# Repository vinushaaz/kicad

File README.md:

# KiCad PCB Design Journey

## About
This repository contains my learning and projects in PCB design using KiCad.  
It shows my progress from basic schematics to complete PCB layouts.

## Tools
- KiCad
- GitHub
- Arduino / Microcontrollers

## Skills Gained
- Schematic design
- Footprint assignment
- PCB layout & routing
- Design Rule Check (DRC)
- Gerber file generation

## Projects
- Queaky Toy circuit
- LED Blinker PCB  
- 4x4 Keypad Interface  
- LCD Interface Circuit  

## Goal
To design and build reliable PCBs for embedded and IoT applications.

## Author
Vinu – Embedded Systems | C/C++ | IoT

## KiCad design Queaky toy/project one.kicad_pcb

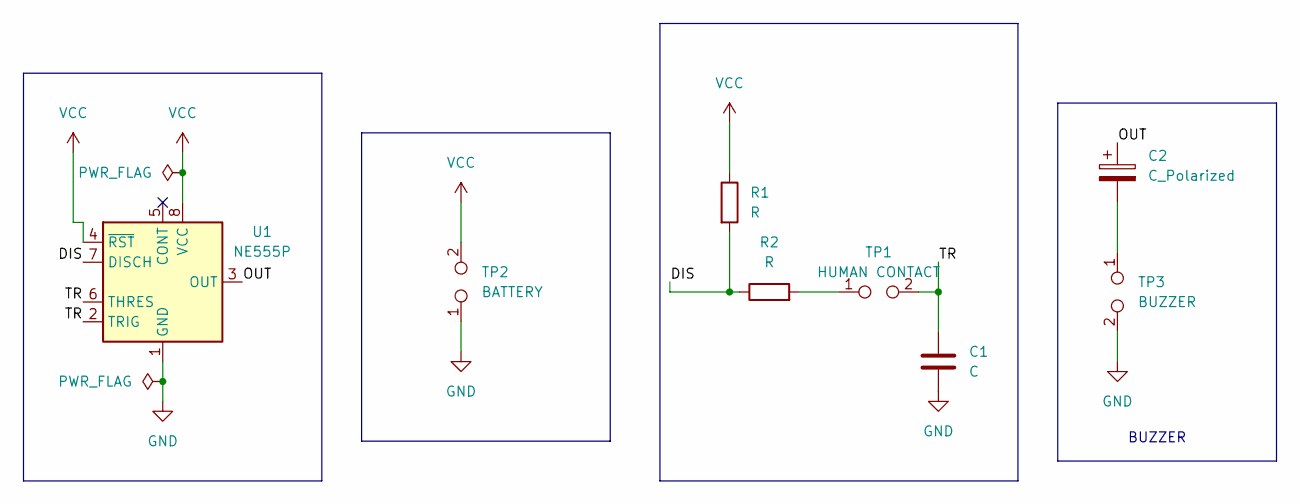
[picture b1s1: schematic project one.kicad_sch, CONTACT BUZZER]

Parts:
C1: C; C_Disc_D7.0mm_W2.5mm_P5.00mm
C2: C_Polarized; CP_Radial_D12.5mm_P5.00mm
R1, R2: R; R_Axial_DIN0309_L9.0mm_D3.2mm_P2.54mm_Vertical
TP1: HUMAN CONTACT; PinSocket_1x02_P2.54mm_Horizontal
TP2: BATTERY; PinSocket_1x02_P2.54mm_Horizontal
TP3: BUZZER; PinSocket_1x02_P2.54mm_Horizontal
U1: NE555P; DIP-8_W7.62mm

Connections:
/DIS: R1.2, R2.1, U1.7 (DISCH)
/OUT: C2.1, U1.3 (OUT)
GND: C1.2, TP2.1, TP3.2, U1.1 (GND)
unnamed: C2.2, TP3.1
unnamed: R2.2, TP1.1
VCC: C1.1, R1.1, TP1.2, TP2.2, U1.2 (TRIG), U1.4 (~RST), U1.6 (THRES), U1.8 (VCC)

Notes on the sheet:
BUZZER

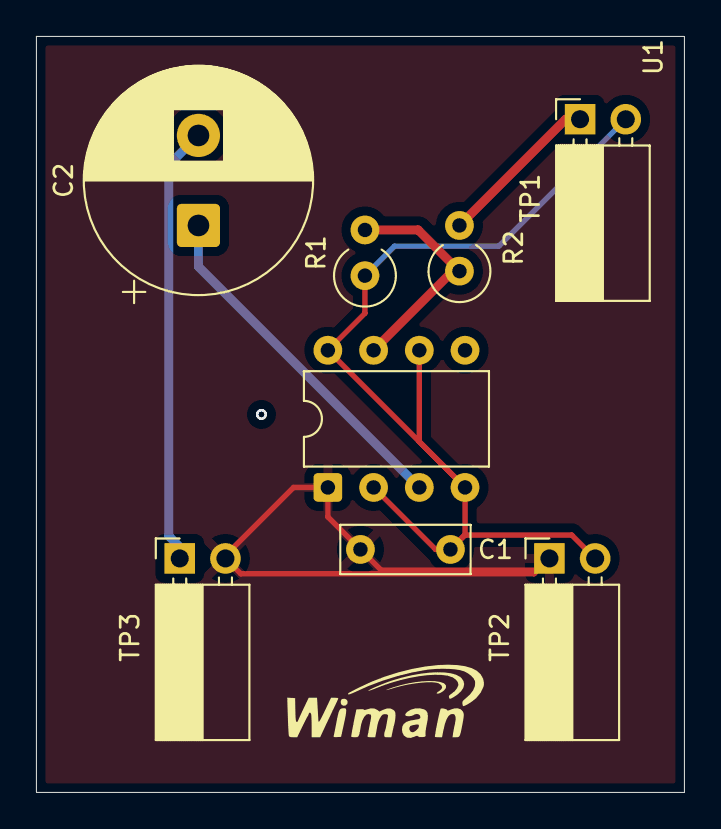
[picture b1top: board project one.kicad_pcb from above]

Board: 2 copper layers, 36.0 x 42.0 mm, 8 parts (0 on the bottom side), 6 nets.

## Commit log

2026-03-30 Revise README to document KiCad journey and goals
    Expanded README to include sections on objectives, tools, learning experiences, and future goals related to PCB design using KiCad.
2026-03-30 Revise README for clarity and conciseness
    Updated the README to streamline content and improve clarity. Removed redundant sections and refined the objectives and skills gained.
